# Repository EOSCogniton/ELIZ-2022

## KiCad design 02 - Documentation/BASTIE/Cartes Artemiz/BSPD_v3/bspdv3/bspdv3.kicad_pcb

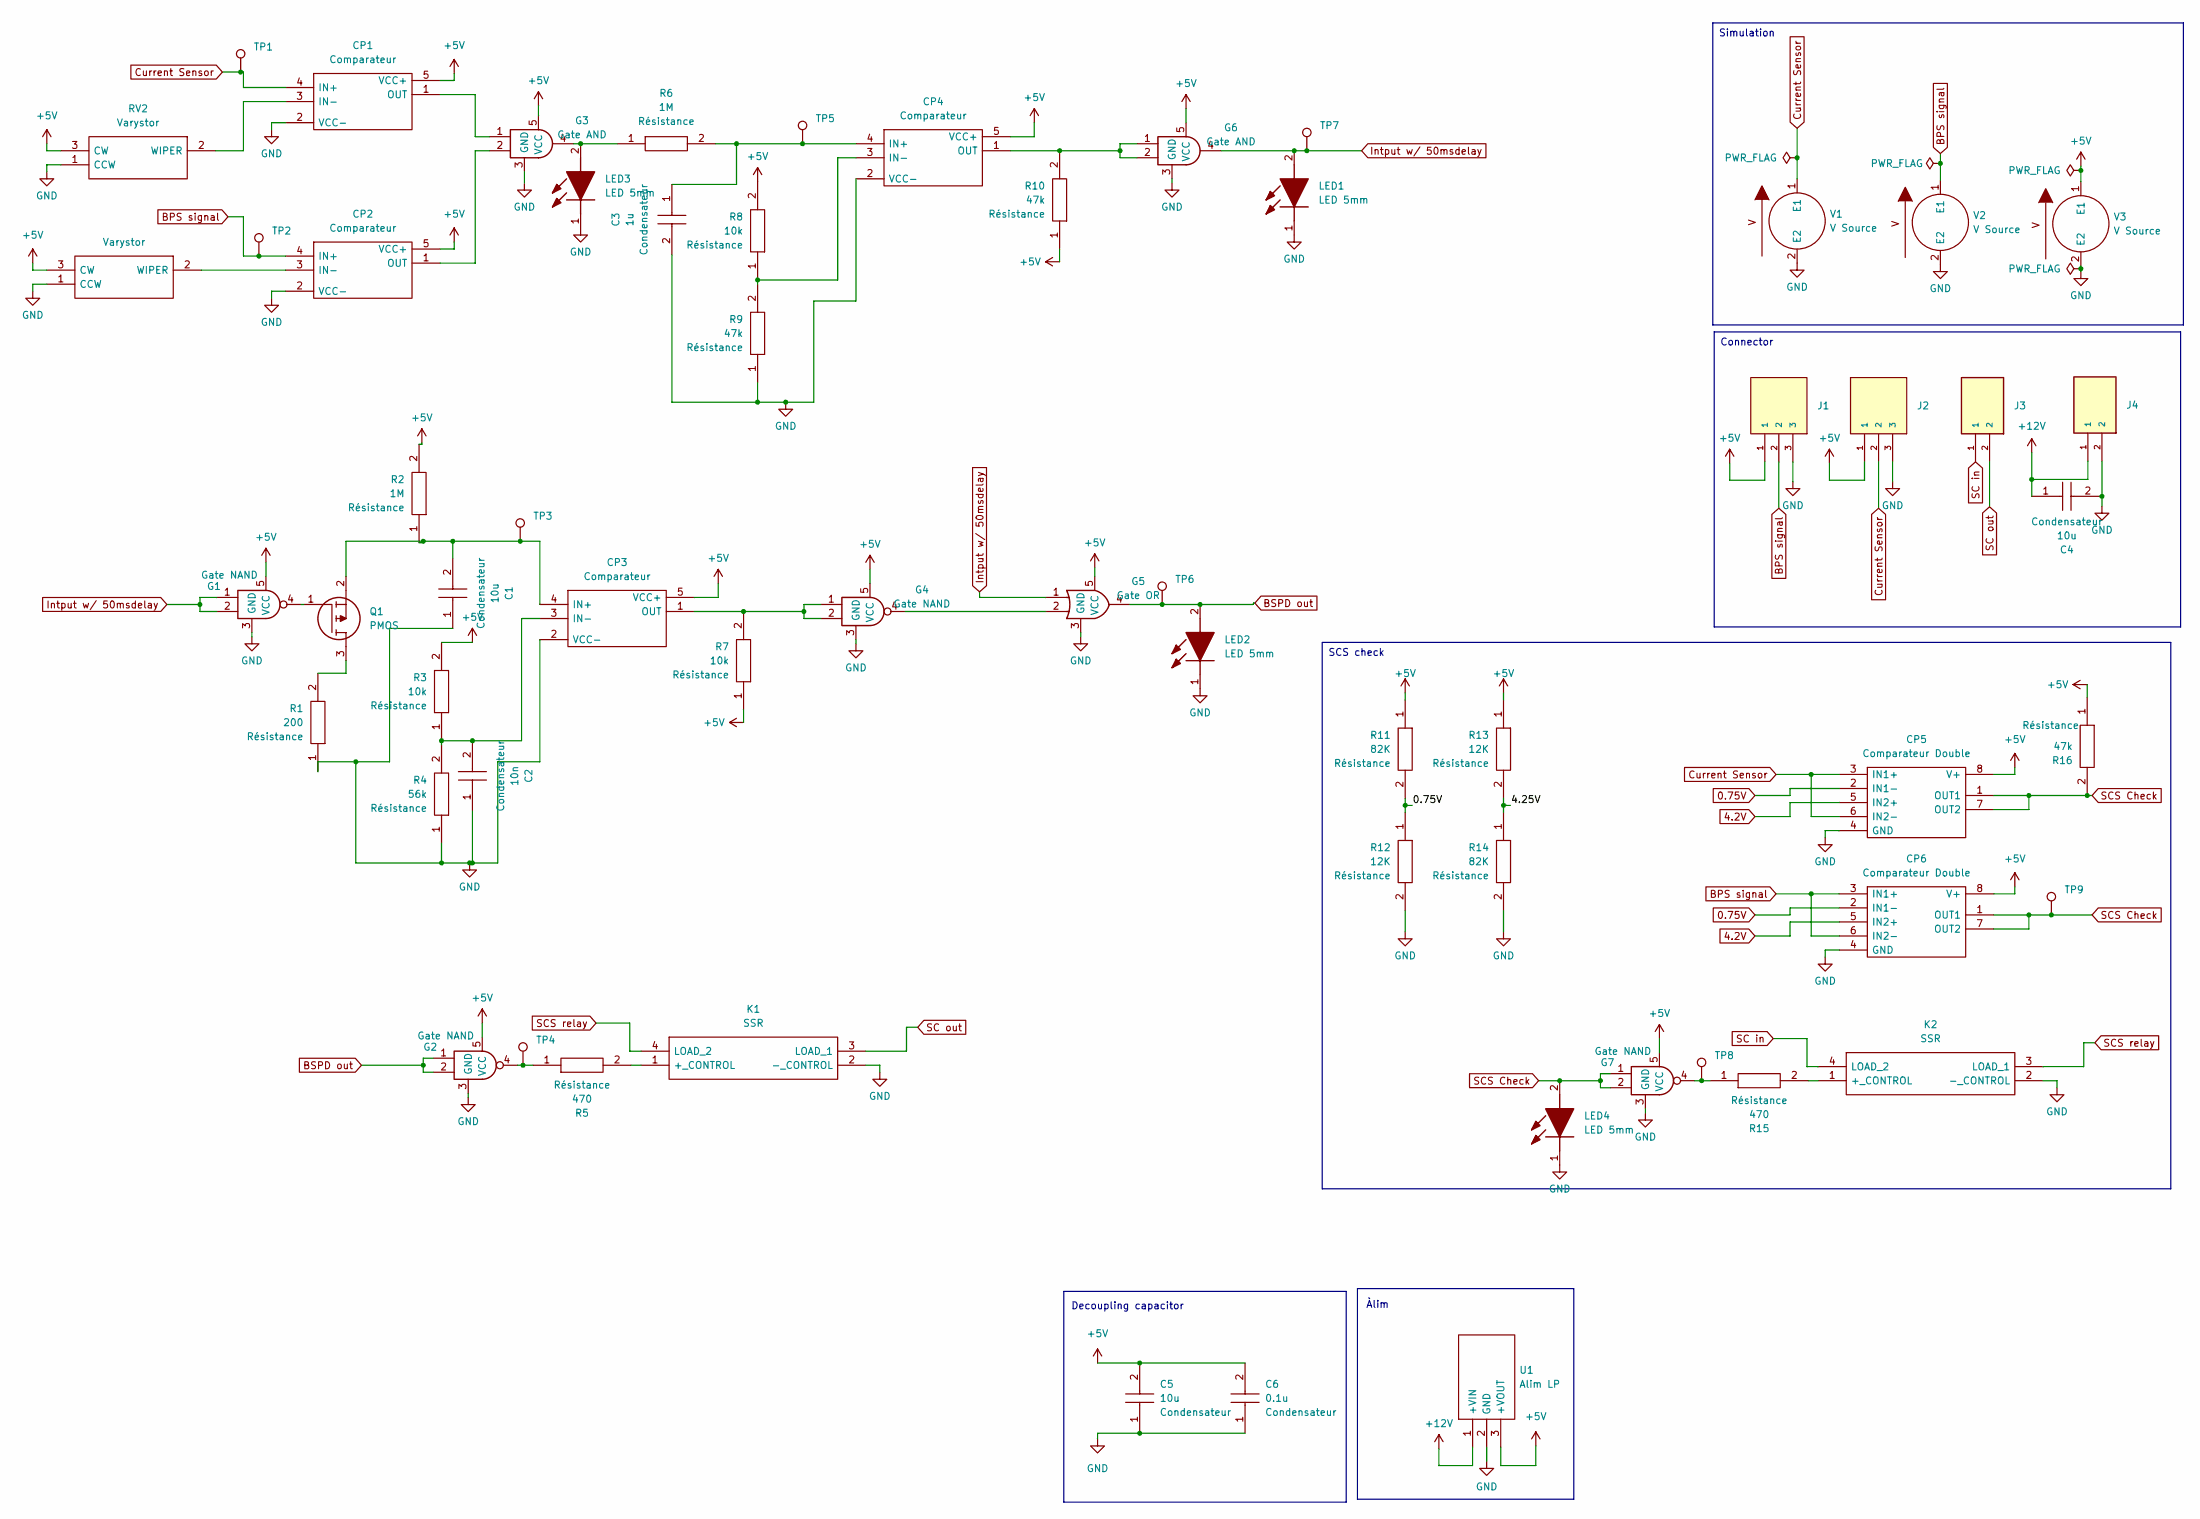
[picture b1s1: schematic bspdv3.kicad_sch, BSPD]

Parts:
C1, C4, C5: 10u; CAPC2012X130N; Manufacturer_Part_Number 0805Y1000104JXT
C2: 10n; CAPC2012X130N; Manufacturer_Part_Number 0805Y1000104JXT
C3: 1u; CAPC2012X130N; Manufacturer_Part_Number 0805Y1000104JXT
C6: 0.1u; CAPC2012X130N; Manufacturer_Part_Number 0805Y1000104JXT
CP1, CP2, CP3, CP4: Comparateur TS391ILT; SOT95P280X145-5N; Manufacturer_Part_Number TS391ILT; Mouser Part Number 511-TS391IL
CP5, CP6: Comparateur Double LM393LVDR; SOIC127P600X175-8N; Manufacturer_Part_Number LM393LVDR; Mouser Part Number 595-LM393LVDR
G1, G2, G4, G7: Gate NAND SN74AHCT1G00DBVR; SOT95P280X145-5N; Manufacturer_Part_Number SN74AHCT1G00DBVR; Mouser Part Number 595-SN74AHCT1G00DBVR
G3, G6: Gate AND SN74AHCT1G08DBVR; SOT95P280X145-5N; Manufacturer_Part_Number SN74AHCT1G08DBVR; Mouser Part Number 595-SN74AHCT1G08DBVR
G5: Gate OR SN74AHCT1G32DBVR; SOT95P280X145-5N; Manufacturer_Part_Number SN74AHCT1G32DBVR; Mouser Part Number 595-SN74AHCT1G32DBVR
J1, J2: 3P Droit 22-11-2032; MOLEX_22-11-2032; Manufacturer_Part_Number 22-11-2032; Mouser Part Number 538-22-11-2032
J3, J4: 2P Droit 2-11-2022; MOLEX_22-11-2022; Manufacturer_Part_Number 22-11-2022; Mouser Part Number 538-22-11-2022
K1, K2: SSR CPC1394GR; CPC1394GR; Manufacturer_Part_Number CPC1394GR; Mouser Part Number 849-CPC1394GR
LED1, LED2, LED3, LED4: LED 5mm; 4302H55V; Mouser Part Number 606-4302H5-5V
Q1: PMOS SI2343CDS-T1-GE3; SOT95P237X112-3N; Manufacturer_Part_Number SI2343CDS-T1-GE3; Mouser Part Number 781-SI2343CDS-T1-GE3
R1: 200; RESC3216X70N; Manufacturer_Part_Number RK73H2BLTDD2152F; Mouser Part Number N/A
R2, R6: 1M; RESC3216X70N; Manufacturer_Part_Number RK73H2BLTDD2152F; Mouser Part Number N/A
R3, R7, R8: 10k; RESC3216X70N; Manufacturer_Part_Number RK73H2BLTDD2152F; Mouser Part Number N/A
R4: 56k; RESC3216X70N; Manufacturer_Part_Number RK73H2BLTDD2152F; Mouser Part Number N/A
R5, R15: 470; RESC3216X70N; Manufacturer_Part_Number RK73H2BLTDD2152F; Mouser Part Number N/A
R9, R10, R16: 47k; RESC3216X70N; Manufacturer_Part_Number RK73H2BLTDD2152F; Mouser Part Number N/A
R11, R14: 82K; RESC3216X70N; Manufacturer_Part_Number RK73H2BLTDD2152F; Mouser Part Number N/A
R12, R13: 12K; RESC3216X70N; Manufacturer_Part_Number RK73H2BLTDD2152F; Mouser Part Number N/A
RV1, RV2: Varystor 3296Y-1-223LF; 3296Y1223LF; Manufacturer_Part_Number 3296Y-1-223LF; Mouser Part Number 652-3296Y-1-223LF
TP1, TP2, TP3, TP4, TP5, TP6, TP7, TP8, TP9: type="R" model="TestPoint" lib=""; TestPoint_Pad_D2.0mm
U1: Alim LP TSR_0.5-2450; AE40UWS12; Manufacturer_Part_Number TSR 0.5-2450; Mouser Part Number 495-TSR0.5-2450
V1, V2, V3: 5

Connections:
0.75V: CP5.2 (IN1-), CP6.2 (IN1-), R11.2, R12.1
4.2V: CP5.5 (IN2+), CP6.5 (IN2+)
+5V: C5.2, C6.2, CP1.5 (VCC+), CP2.5 (VCC+), CP3.5 (VCC+), CP4.5 (VCC+), CP5.8 (V+), CP6.8 (V+), G1.5 (VCC), G2.5 (VCC), G3.5 (VCC), G4.5 (VCC), G5.5 (VCC), G6.5 (VCC), G7.5 (VCC), J1.1, J2.1, R2.2, R3.2, R7.1, R8.2, R10.1, R11.1, R13.1, R16.1, RV1.3 (CW), RV2.3 (CW), U1.3 (+VOUT), V3.1 (E1); also elsewhere on the board
+12V: C4.1, J4.1, U1.1 (+VIN); also elsewhere on the board
/4.25V: R13.2, R14.1
BPS signal: CP2.4 (IN+), CP6.3 (IN1+), CP6.6 (IN2-), J1.2, TP2.1, V2.1 (E1); also elsewhere on the board
BSPD out: G2.1, G2.2, G5.4, LED2.2 (A), TP6.1
Current Sensor: CP1.4 (IN+), CP5.3 (IN1+), CP5.6 (IN2-), J2.2, TP1.1, V1.1 (E1); also elsewhere on the board
GND: C1.1, C2.1, C3.2, C4.2, C5.1, C6.1, CP1.2 (VCC-), CP2.2 (VCC-), CP3.2 (VCC-), CP4.2 (VCC-), CP5.4 (GND), CP6.4 (GND), G1.3 (GND), G2.3 (GND), G3.3 (GND), G4.3 (GND), G5.3 (GND), G6.3 (GND), G7.3 (GND), J1.3, J2.3, J4.2, K1.2 (-_CONTROL), K2.2 (-_CONTROL), LED1.1 (K), LED2.1 (K), LED3.1 (K), LED4.1 (K), R1.1, R4.1, R9.1, R12.2, R14.2, RV1.1 (CCW), RV2.1 (CCW), U1.2 (GND), V1.2 (E2), V2.2 (E2), V3.2 (E2); also elsewhere on the board
Intput w/ 50msdelay: G1.1, G1.2, G5.1, G6.4, LED1.2 (A), TP7.1
unnamed: CP1.3 (IN-), RV2.2 (WIPER)
unnamed: CP1.1 (OUT), G3.1
unnamed: CP2.3 (IN-), RV1.2 (WIPER)
unnamed: CP2.1 (OUT), G3.2
unnamed: C1.2, CP3.4 (IN+), Q1.2, R2.1, TP3.1
unnamed: C2.2, CP3.3 (IN-), R3.1, R4.2
unnamed: CP3.1 (OUT), G4.1, G4.2, R7.2
unnamed: C3.1, CP4.4 (IN+), R6.2, TP5.1
unnamed: CP4.3 (IN-), R8.1, R9.2
unnamed: CP4.1 (OUT), G6.1, G6.2, R10.2
unnamed: G1.4, Q1.1
unnamed: G2.4, R5.1, TP4.1
unnamed: G4.4, G5.2
unnamed: G7.4, R15.1, TP8.1
unnamed: K1.1 (+_CONTROL), R5.2
unnamed: K2.1 (+_CONTROL), R15.2
unnamed: G3.4, LED3.2 (A), R6.1
unnamed: Q1.3, R1.2
SC in: J3.1, K2.4 (LOAD_2)
SC out: J3.2, K1.3 (LOAD_1)
SCS Check: CP5.1 (OUT1), CP5.7 (OUT2), CP6.1 (OUT1), CP6.7 (OUT2), G7.1, G7.2, LED4.2 (A), R16.2, TP9.1
SCS relay: K1.4 (LOAD_2), K2.3 (LOAD_1)

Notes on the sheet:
Connector
SCS check
Simulation
Àlim
Decoupling capacitor

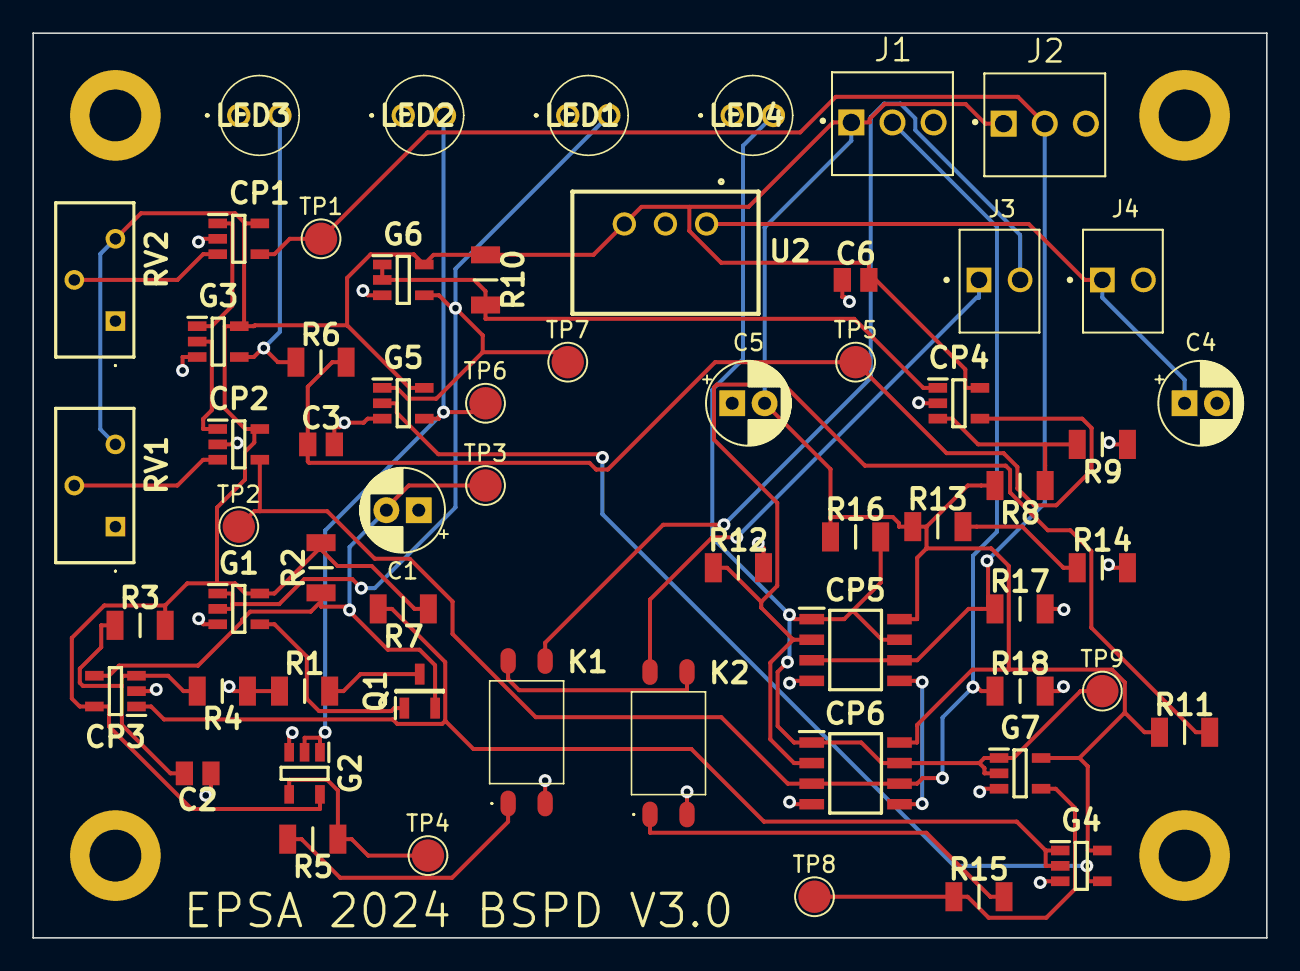
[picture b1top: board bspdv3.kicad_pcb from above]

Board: 2 copper layers, 76.2 x 55.9 mm, 64 parts (0 on the bottom side), 32 nets.

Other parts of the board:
M1, M2, M3, M4: MountingHole_3.2mm_M3_DIN965_Pad
R17, R18: 470k; RESC3216X70N
U2: Alim LP TSR_0.5-2450; TSR-0.5-2433

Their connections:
+5V: U2.3 (+VOUT); also elsewhere on the board
+12V: U2.1 (+VIN); also elsewhere on the board
BPS signal: R18.1; also elsewhere on the board
Current Sensor: R17.1; also elsewhere on the board
GND: R17.2, R18.2, U2.2 (GND); also elsewhere on the board

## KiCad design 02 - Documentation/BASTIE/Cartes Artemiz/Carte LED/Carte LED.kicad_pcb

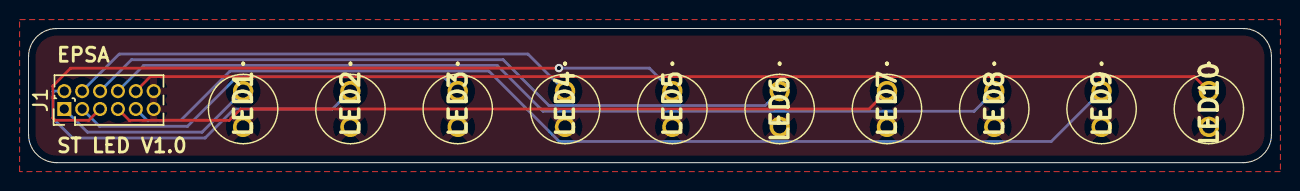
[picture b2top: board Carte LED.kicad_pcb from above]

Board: 2 copper layers, 88.3 x 9.5 mm, 11 parts (0 on the bottom side), 11 nets.

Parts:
J1: Conn_02x06_Counter_Clockwise; PinHeader_2x06_P1.27mm_Vertical
LED1, LED2, LED3, LED4, LED5, LED6, LED7, LED8, LED9, LED10: 4302H5-5V; 4302H55V

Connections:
GND: J1.11, J1.12, LED1.2, LED2.2, LED3.2, LED4.2, LED5.2, LED6.2, LED7.2, LED8.2, LED9.2, LED10.2
LED 1: J1.1, LED1.1
LED 2: J1.2, LED2.1
LED 3: J1.3, LED3.1
LED 4: J1.4, LED4.1
LED 5: J1.5, LED5.1
LED 6: J1.6, LED6.1
LED 7: J1.7, LED7.1
LED 8: J1.8, LED8.1
LED 9: J1.9, LED9.1
LED 10: J1.10, LED10.1

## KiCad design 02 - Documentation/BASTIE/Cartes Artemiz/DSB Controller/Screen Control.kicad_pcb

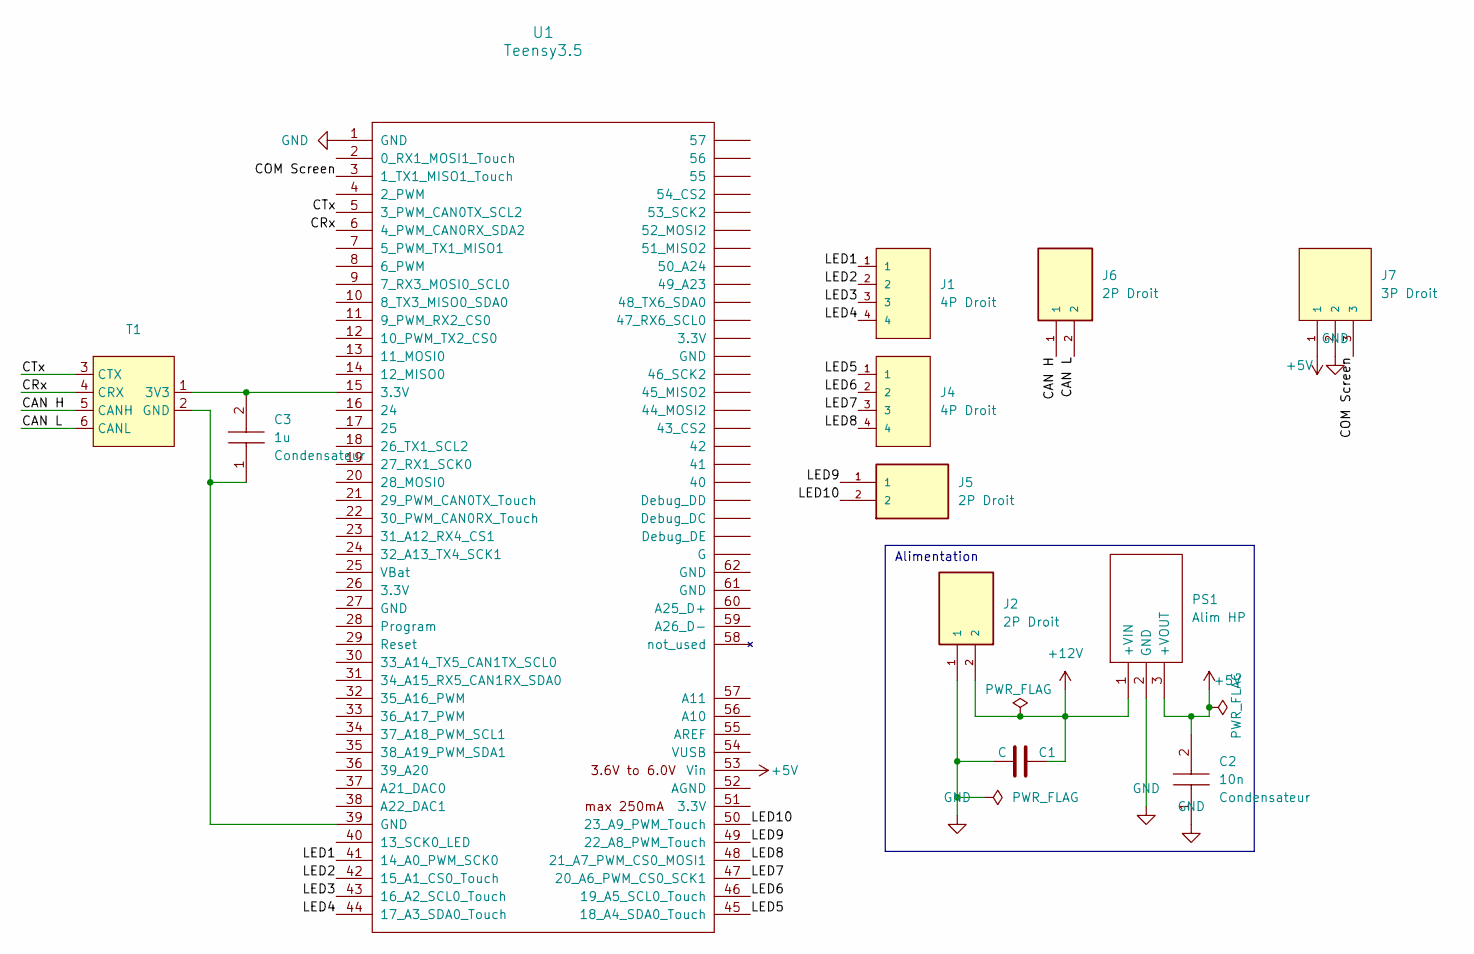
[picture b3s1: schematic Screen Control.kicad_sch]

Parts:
C1: C; CP_Radial_D5.0mm_P2.00mm
C2: 10n; CAPC2012X130N; Manufacturer_Part_Number 0805Y1000104JXT
C3: 1u; CAPC2012X130N; Manufacturer_Part_Number 0805Y1000104JXT
J1, J4: 4P Droit 22-11-2042; MOLEX_22-11-2042; Manufacturer_Part_Number 22-11-2042; Mouser Part Number 538-22-11-2042
J2, J5, J6: 2P Droit 2-11-2022; MOLEX_22-11-2022; PARTREV BD8
J7: 3P Droit 22-11-2032; MOLEX_22-11-2032; Manufacturer_Part_Number 22-11-2032; Mouser Part Number 538-22-11-2032
PS1: Alim HP TSR_2-2450; TSR-2; Manufacturer_Part_Number TSR 2-2450; Mouser Part Number 495-TSR2-2450
T1: CAN_Transceiver
U1: Teensy3.5; Teensy35_36

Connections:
+5V: C2.2, J7.1, PS1.3 (+VOUT), U1.53 (Vin)
+12V: C1.2, J2.2, PS1.1 (+VIN)
/CAN H: J6.1, T1.5 (CANH)
/CAN L: J6.2, T1.6 (CANL)
/COM Screen: J7.3, U1.3 (1_TX1_MISO1_Touch)
/CRx: T1.4 (CRX), U1.6 (4_PWM_CAN0RX_SDA2)
/CTx: T1.3 (CTX), U1.5 (3_PWM_CAN0TX_SCL2)
/LED1: J1.1, U1.41 (14_A0_PWM_SCK0)
/LED2: J1.2, U1.42 (15_A1_CS0_Touch)
/LED3: J1.3, U1.43 (16_A2_SCL0_Touch)
/LED4: J1.4, U1.44 (17_A3_SDA0_Touch)
/LED5: J4.1, U1.45 (18_A4_SDA0_Touch)
/LED6: J4.2, U1.46 (19_A5_SCL0_Touch)
/LED7: J4.3, U1.47 (20_A6_PWM_CS0_SCK1)
/LED8: J4.4, U1.48 (21_A7_PWM_CS0_MOSI1)
/LED9: J5.1, U1.49 (22_A8_PWM_Touch)
/LED10: J5.2, U1.50 (23_A9_PWM_Touch)
GND: C1.1, C2.1, J2.1, J7.2, PS1.2 (GND), U1.1 (GND)
unnamed: C3.2, T1.1 (3V3), U1.15 (3.3V)
unnamed: C3.1, T1.2 (GND), U1.39 (GND)

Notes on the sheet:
Alimentation

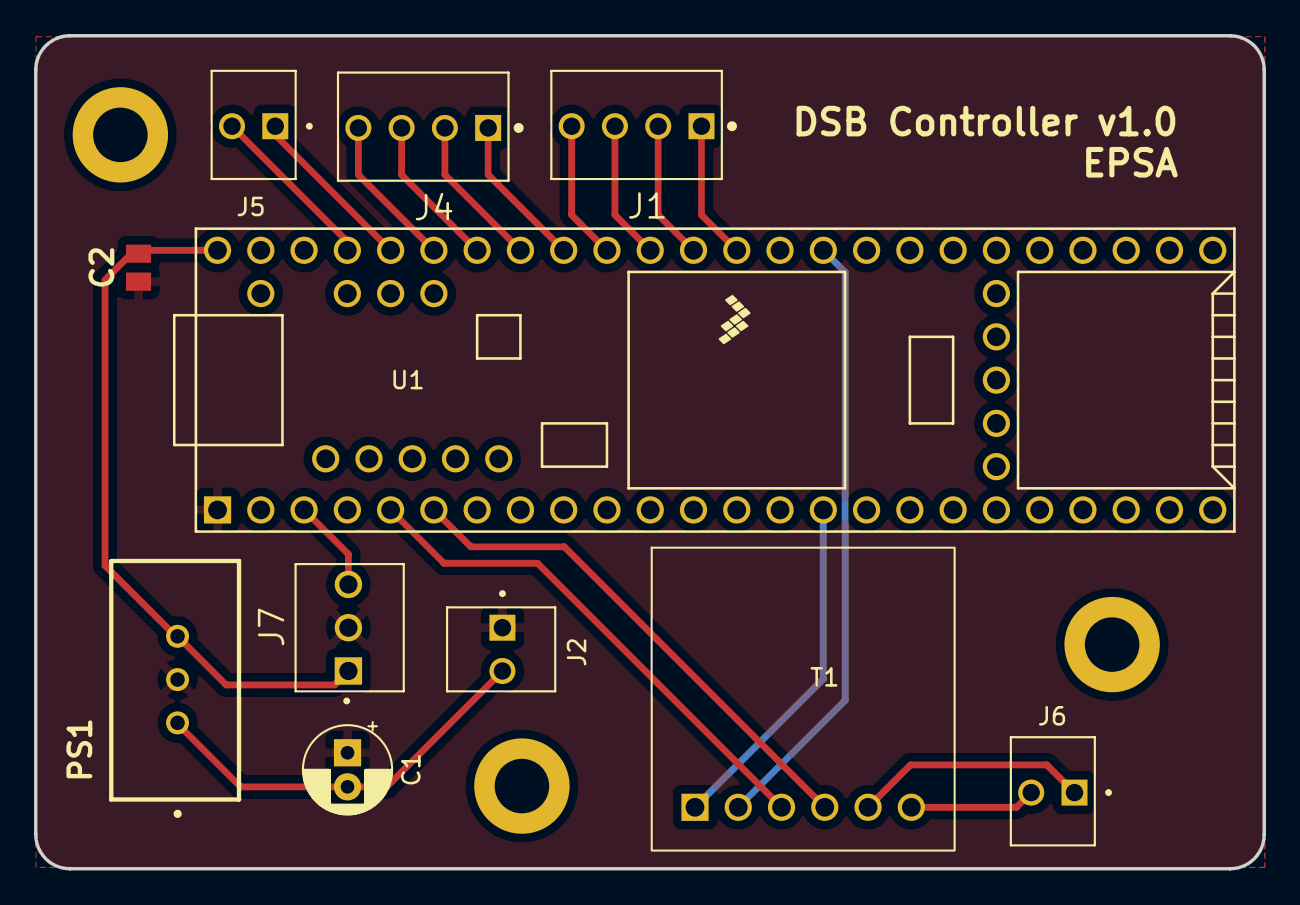
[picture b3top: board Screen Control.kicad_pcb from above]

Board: 2 copper layers, 72.1 x 48.9 mm, 11 parts (0 on the bottom side), 20 nets.

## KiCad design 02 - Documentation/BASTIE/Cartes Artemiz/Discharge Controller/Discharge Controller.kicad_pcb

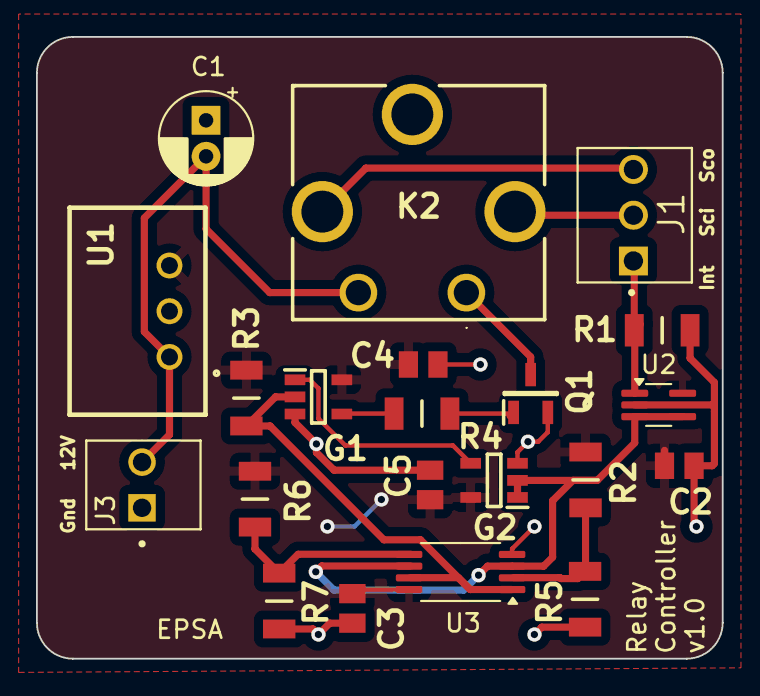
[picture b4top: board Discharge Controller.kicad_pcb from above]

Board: 2 copper layers, 38.1 x 34.5 mm, 21 parts (0 on the bottom side), 14 nets.

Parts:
C1: C; CP_Radial_D5.0mm_P2.00mm
C2, C3, C4, C5: 10n; CAPC2012X130N
G1: Gate AND SN74AHCT1G08DBVR; SOT95P280X145-5N
G2: Gate NAND SN74AHCT1G00DBVR; SOT95P280X145-5N
J1: 3P Droit 22-11-2032; MOLEX_22-11-2032
J3: 2P Droit 2-11-2022; MOLEX_22-11-2022
K2: Relais PCB; CP112V
Q1: NMOS SQ2348ES-T1_GE3; SOT95P237X112-3N
R1: 500k; RESC3216X70N
R2, R7: 82k; RESC3216X70N
R3: 10k; RESC3216X70N
R4: 1k; RESC3216X70N
R5, R6: 12k; RESC3216X70N
U1: Alim LP TSR_0.5-2450; TSR-0.5-2433
U2: SOT-353_SC-70-5_Handsoldering
U3: Opamp_Dual; TSSOP-8_4.4x3mm_P0.65mm

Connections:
+5V: C2.2, C3.2, C4.2, C5.2, G1.5 (VCC), G2.5 (VCC), R2.2, R3.1, R6.2, U1.3 (+VOUT), U2.5 (V+), U3.8 (V+)
+12V: C1.2, J3.2, K2.5, U1.1 (+VIN)
/0.75V: R2.1, R5.2, U3.2 (-)
/4.25V: R6.1, R7.2, U3.5 (+)
/Raw_Relay_Closed: J1.1, R1.1, U2.1 (+)
/Relay_Closed: G2.1, G2.2, U2.3 (-), U2.4, U3.3 (+), U3.6 (-)
/SC in: J1.2, K2.2
/SC out: J1.3, K2.4
/SCS_Compliance: G1.2, R3.2, U3.1, U3.7
GND: C1.1, C2.1, C3.1, C4.1, C5.1, G1.3 (GND), G2.3 (GND), J3.1, Q1.2, R1.2, R5.1, R7.1, U1.2 (GND), U2.2 (V-), U3.4 (V-)
unnamed: G1.1, G2.4
unnamed: G1.4, R4.1
unnamed: K2.1, Q1.3
unnamed: Q1.1, R4.2

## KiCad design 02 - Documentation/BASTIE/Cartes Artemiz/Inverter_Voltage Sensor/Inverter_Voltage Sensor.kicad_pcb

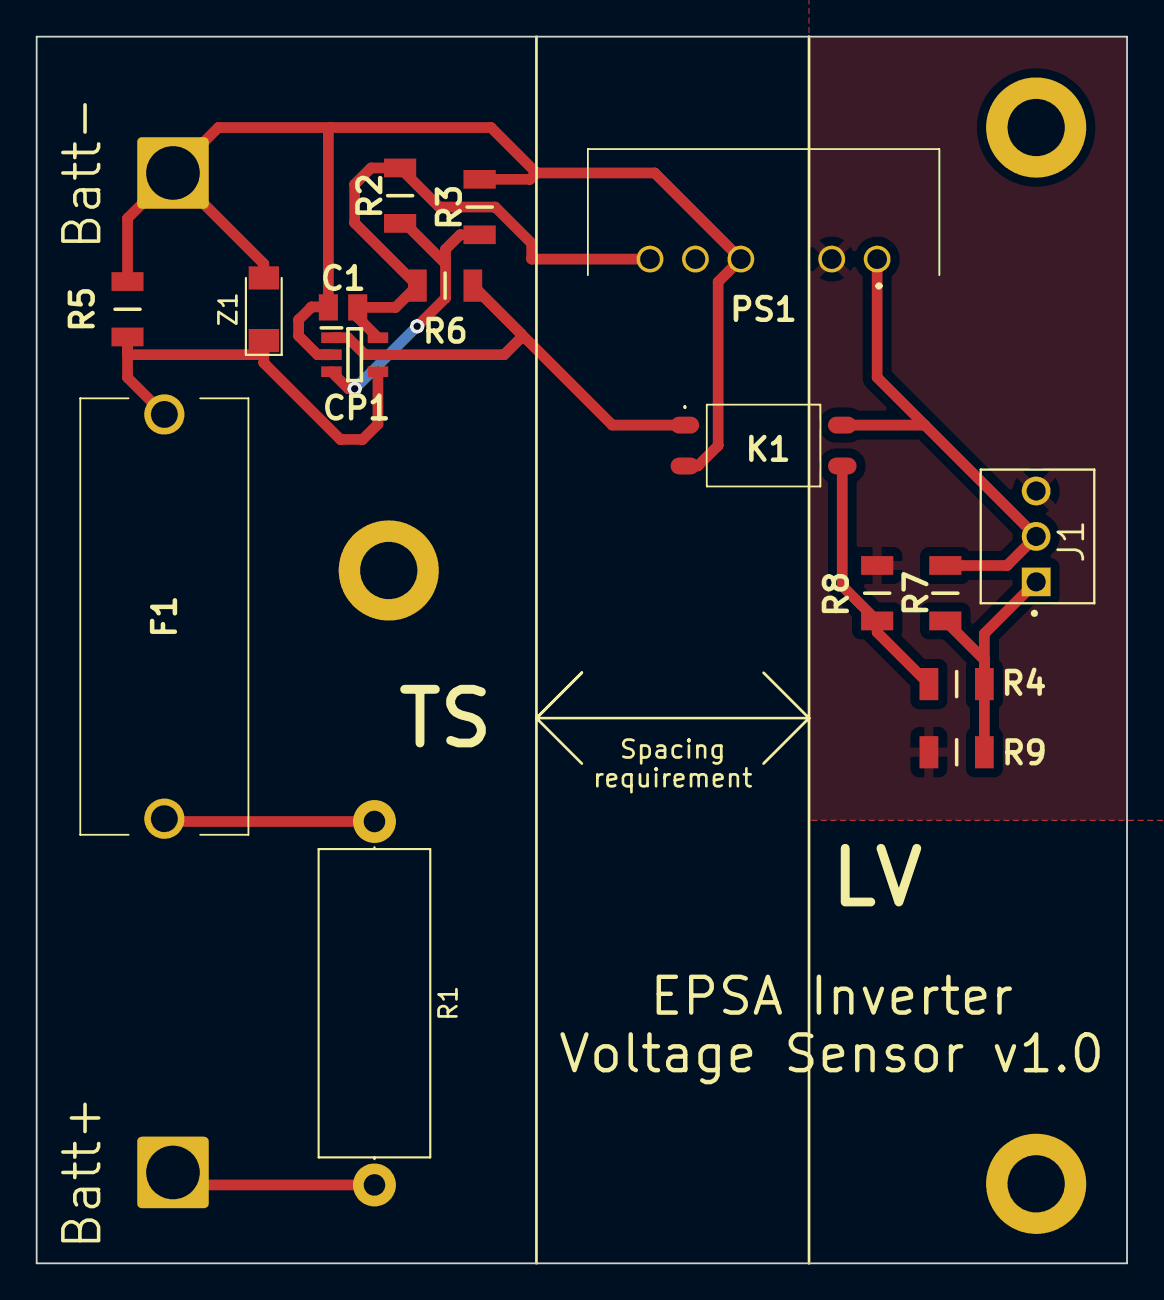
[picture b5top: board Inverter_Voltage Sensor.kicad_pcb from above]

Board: 2 copper layers, 61.0 x 68.6 mm, 18 parts (0 on the bottom side), 11 nets.

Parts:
C1: Condensateur 0805Y1000104JXT; CAPC2012X130N
CP1: Comparateur TS391ILT; SOT95P280X145-5N
F1: Fuse; 0PTF0078P
J1: 3P Droit 22-11-2032; MOLEX_22-11-2032
K1: SSR CPC1394GR; CPC1394GR
PS1: Alim Iso PDM2-S5-S5-S; PDM2S5S5S
R1: 820k; R_Axial_DIN0617_L17.0mm_D6.0mm_P20.32mm_Horizontal
R2: 1k2; RESC3216X70N
R3: 1k; RESC3216X70N
R4: 3k9; RESC3216X70N
R5: 33k; RESC3216X70N
R6: 2k7; RESC3216X70N
R7: 2k; RESC3216X70N
R8, R9: 8k2; RESC3216X70N
TP1, TP2: type="R" model="TestPoint" lib=""; SolderWire-2.5sqmm_1x01_D2.4mm_OD3.6mm
Z1: Zener TZM5224B-GS08; D_MiniMELF

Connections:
0: C1.1, CP1.2 (VCC-), K1.2 (-_CONTROL), PS1.4 (0V), R3.2, R5.1, TP2.1, Z1.2
+5V: C1.2, CP1.5 (VCC+), PS1.6 (+VO), R2.2, R6.2
+5VA: J1.2, K1.4 (LOAD_2), PS1.1 (VIN), R8.2
+BATT: R1.2, TP1.1
Comp: CP1.1 (OUT), K1.1 (+_CONTROL), R6.1
Exit: J1.1, R4.2, R8.1, R9.2
GND: J1.3, PS1.2 (GND), R7.1, R9.1
unnamed: CP1.4 (IN+), F1.2, R5.2, Z1.1
unnamed: CP1.3 (IN-), R2.1, R3.1
unnamed: F1.1, R1.1
Raw_Exit: K1.3 (LOAD_1), R4.1, R7.2

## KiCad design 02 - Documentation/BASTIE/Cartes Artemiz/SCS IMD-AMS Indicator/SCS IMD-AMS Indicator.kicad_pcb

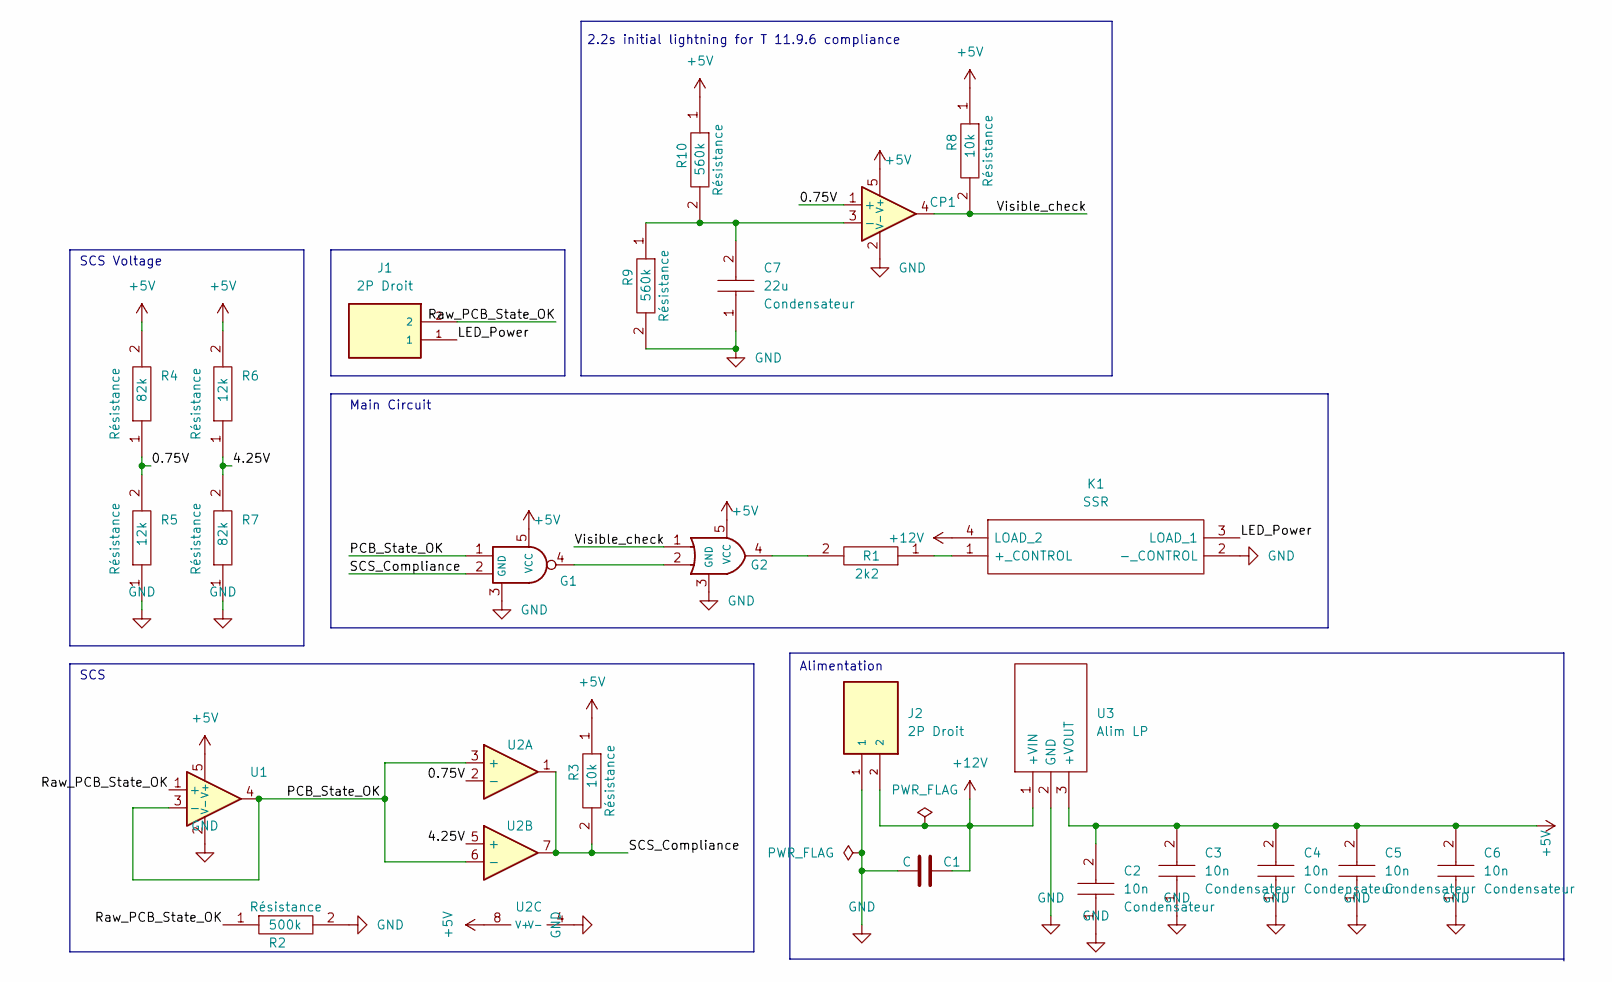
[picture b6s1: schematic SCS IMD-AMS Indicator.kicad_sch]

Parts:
C1: C; CP_Radial_D5.0mm_P2.00mm
C2, C3, C4, C5, C6: 10n; CAPC2012X130N; Manufacturer_Part_Number 0805Y1000104JXT
C7: 22u; CAPC2012X130N; Manufacturer_Part_Number 0805Y1000104JXT
CP1: Comparator; SOT-353_SC-70-5; Manufacturer_Part_Number LMV331M7/NOPB; Mouser Part Number 926-LMV331M7/NOPB
G1: Gate NAND SN74AHCT1G00DBVR; SOT95P280X145-5N; Manufacturer_Part_Number SN74AHCT1G00DBVR; Mouser Part Number 595-SN74AHCT1G00DBVR
G2: Gate OR SN74AHCT1G32DBVR; SOT95P280X145-5N; Manufacturer_Part_Number SN74AHCT1G32DBVR; Mouser Part Number 595-SN74AHCT1G32DBVR
J1, J2: 2P Droit 2-11-2022; MOLEX_22-11-2022; PARTREV BD8
K1: SSR CPC1394GR; CPC1394GR; Manufacturer_Part_Number CPC1394GR; Mouser Part Number 849-CPC1394GR
R1: 2k2; RESC3216X70N; Manufacturer_Part_Number RK73H2BLTDD2152F; Mouser Part Number N/A
R2: 500k; RESC3216X70N; Manufacturer_Part_Number RK73H2BLTDD2152F; Mouser Part Number N/A
R3, R8: 10k; RESC3216X70N; Manufacturer_Part_Number RK73H2BLTDD2152F; Mouser Part Number N/A
R4, R7: 82k; RESC3216X70N; Manufacturer_Part_Number RK73H2BLTDD2152F; Mouser Part Number N/A
R5, R6: 12k; RESC3216X70N; Manufacturer_Part_Number RK73H2BLTDD2152F; Mouser Part Number N/A
R9, R10: 560k; RESC3216X70N; Manufacturer_Part_Number RK73H2BLTDD2152F; Mouser Part Number N/A
U1: ${SIM.PARAMS}; SOT-353_SC-70-5_Handsoldering; Manufacturer_Part_Number TLV9061QDCKRQ1; Mouser Part Number 595-TLV9061QDCKRQ1
U2: Opamp_Dual; TSSOP-8_4.4x3mm_P0.65mm; Manufacturer_Part_Number LMV393IPWR; Mouser Part Number 595-LMV393IPWR
U3: Alim LP TSR_0.5-2450; TSR-0.5-2433; Manufacturer_Part_Number TSR 0.5-2450; Mouser Part Number 495-TSR0.5-2450

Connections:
+5V: C2.2, C3.2, C4.2, C5.2, C6.2, CP1.5 (V+), G1.5 (VCC), G2.5 (VCC), R3.1, R4.2, R6.2, R8.1, R10.1, U1.5 (V+), U2.8 (V+), U3.3 (+VOUT)
+12V: C1.2, J2.2, K1.4 (LOAD_2), U3.1 (+VIN)
/0.75V: CP1.1 (+), R4.1, R5.2, U2.2 (-)
/4.25V: R6.1, R7.2, U2.5 (+)
/LED_Power: J1.1, K1.3 (LOAD_1)
/PCB_State_OK: G1.1, U1.3 (-), U1.4, U2.3 (+), U2.6 (-)
/Raw_PCB_State_OK: J1.2, R2.1, U1.1 (+)
/SCS_Compliance: G1.2, R3.2, U2.1, U2.7
/Visible_check: CP1.4, G2.1, R8.2
GND: C1.1, C2.1, C3.1, C4.1, C5.1, C6.1, C7.1, CP1.2 (V-), G1.3 (GND), G2.3 (GND), J2.1, K1.2 (-_CONTROL), R2.2, R5.1, R7.1, R9.2, U1.2 (V-), U2.4 (V-), U3.2 (GND)
unnamed: C7.2, CP1.3 (-), R9.1, R10.2
unnamed: G1.4, G2.2
unnamed: G2.4, R1.2
unnamed: K1.1 (+_CONTROL), R1.1

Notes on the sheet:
Alimentation
Main Circuit
SCS
SCS Voltage
2.2s initial lightning for T 11.9.6 compliance

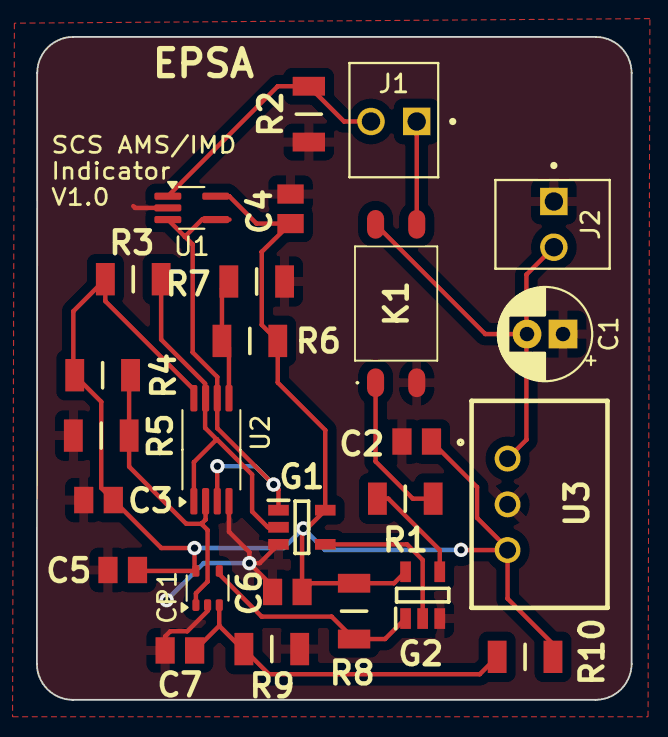
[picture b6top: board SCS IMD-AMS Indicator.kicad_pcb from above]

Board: 2 copper layers, 33.0 x 36.8 mm, 26 parts (0 on the bottom side), 14 nets.

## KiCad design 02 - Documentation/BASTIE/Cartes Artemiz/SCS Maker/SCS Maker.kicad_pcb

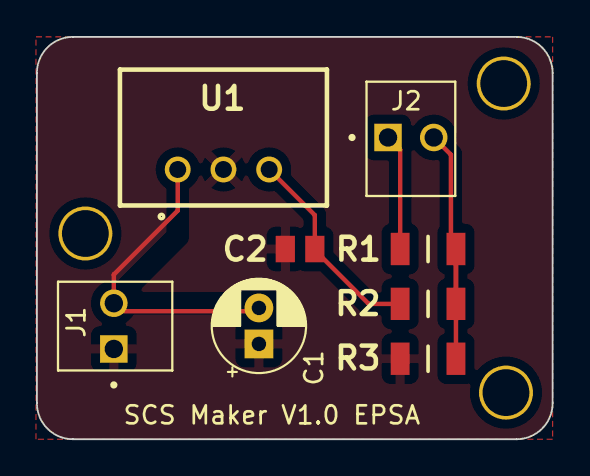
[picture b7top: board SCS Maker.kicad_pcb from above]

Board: 2 copper layers, 28.7 x 22.4 mm, 8 parts (0 on the bottom side), 5 nets.

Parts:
C1: C; CP_Radial_D5.0mm_P2.00mm
C2: 10n; CAPC2012X130N
J1, J2: 2P Droit 2-11-2022; MOLEX_22-11-2022
R1: 3k9; RESC3216X70N
R2, R3: 8k2; RESC3216X70N
U1: Alim LP TSR_0.5-2450; TSR-0.5-2433

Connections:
+5V: C2.2, R2.2, U1.3 (+VOUT)
+12V: C1.2, J1.2, U1.1 (+VIN)
/Output SCS: J2.2, R1.2, R2.1, R3.2
/Sensor Output: J2.1, R1.1
GND: C1.1, C2.1, J1.1, R3.1, U1.2 (GND)
